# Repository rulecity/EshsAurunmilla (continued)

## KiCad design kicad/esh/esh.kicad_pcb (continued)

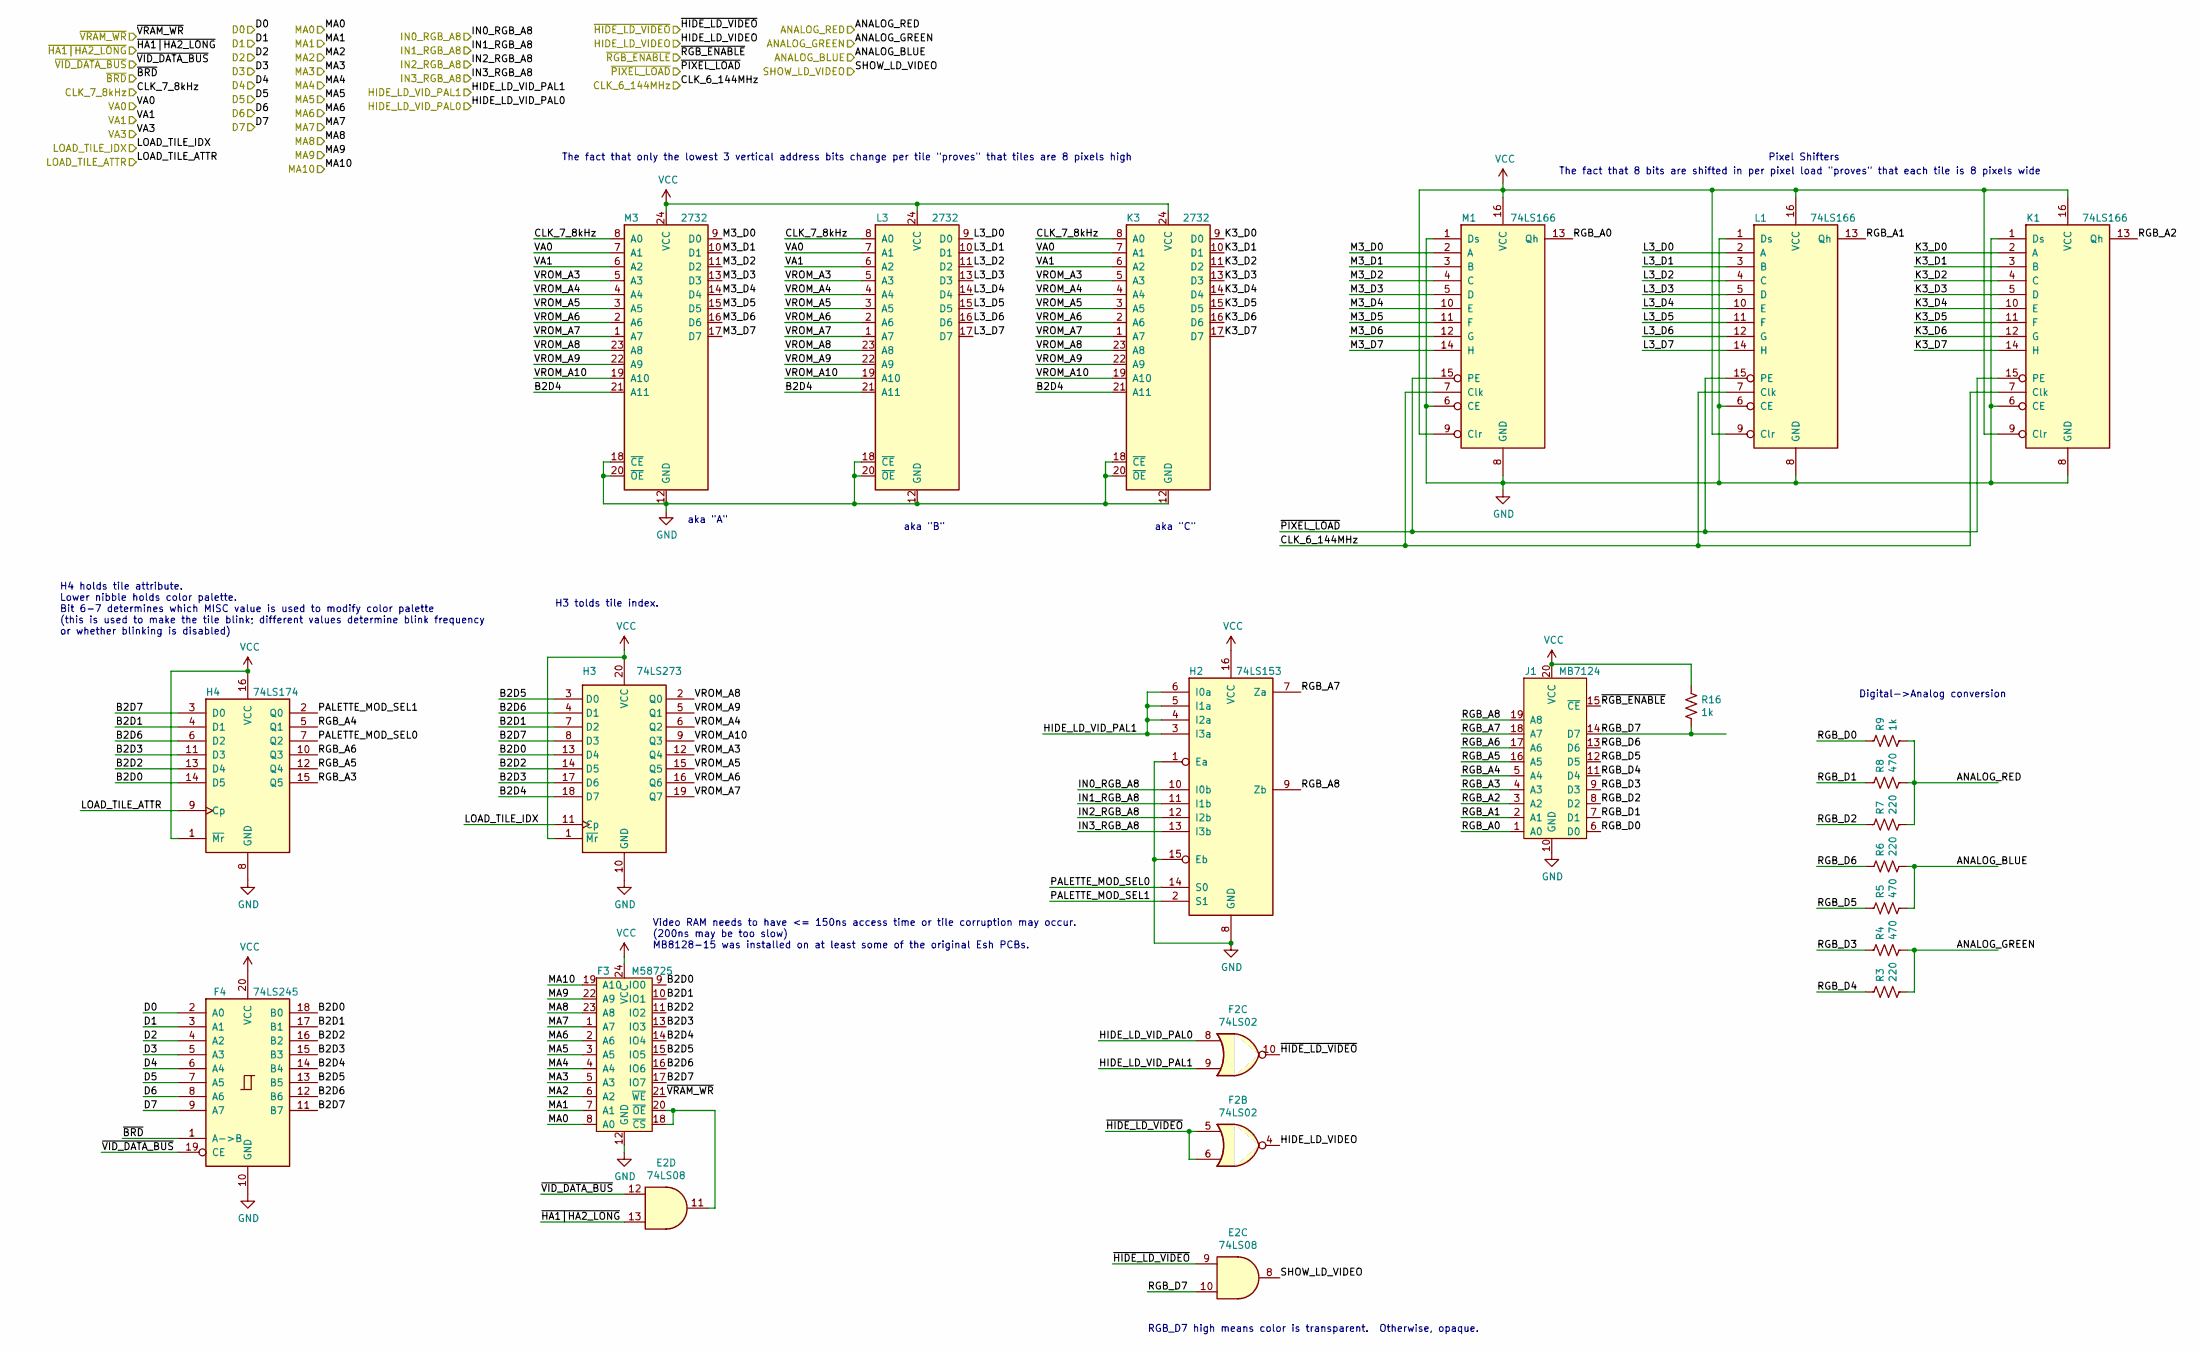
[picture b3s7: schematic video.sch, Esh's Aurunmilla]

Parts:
E2: 74LS08; DIP-14_W7.62mm_Socket
F2: 74LS02; DIP-14_W7.62mm_Socket
F3: M58725; DIP-24_W15.24mm_Socket
F4: 74LS245; DIP-20_W7.62mm_Socket
H2: 74LS153; DIP-16_W7.62mm_Socket
H3: 74LS273; DIP-20_W7.62mm_Socket
H4: 74LS174; DIP-16_W7.62mm_Socket
J1: MB7124; DIP-20_W7.62mm_Socket
K1: 74LS166; DIP-16_W7.62mm_Socket
K3: 2732; DIP-24_W15.24mm_Socket
L1: 74LS166; DIP-16_W7.62mm_Socket
L3: 2732; DIP-24_W15.24mm_Socket
M1: 74LS166; DIP-16_W7.62mm_Socket
M3: 2732; DIP-24_W15.24mm_Socket
R3, R6, R7: 220; R_Axial_DIN0207_L6.3mm_D2.5mm_P10.16mm_Horizontal
R4, R5, R8: 470; R_Axial_DIN0207_L6.3mm_D2.5mm_P10.16mm_Horizontal
R9, R16: 1k; R_Axial_DIN0207_L6.3mm_D2.5mm_P10.16mm_Horizontal

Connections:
/ANALOG_BLUE: R5.2, R6.2; also elsewhere on the board
/ANALOG_GREEN: R3.2, R4.2; also elsewhere on the board
/ANALOG_RED: R7.2, R8.2, R9.2; also elsewhere on the board
/CLK_6_144MHz: K1.7 (Clk), L1.7 (Clk), M1.7 (Clk); also elsewhere on the board
/CLK_7_8kHz: K3.8 (A0), L3.8 (A0), M3.8 (A0); also elsewhere on the board
/D0: F4.2 (A0); also elsewhere on the board
/D1: F4.3 (A1); also elsewhere on the board
/D2: F4.4 (A2); also elsewhere on the board
/D3: F4.5 (A3); also elsewhere on the board
/D4: F4.6 (A4); also elsewhere on the board
/D5: F4.7 (A5); also elsewhere on the board
/D6: F4.8 (A6); also elsewhere on the board
/D7: F4.9 (A7); also elsewhere on the board
/HIDE_LD_VIDEO: F2.4; also elsewhere on the board
/HIDE_LD_VID_PAL0: F2.8; also elsewhere on the board
/HIDE_LD_VID_PAL1: F2.9, H2.3 (I3a), H2.4 (I2a), H2.5 (I1a), H2.6 (I0a); also elsewhere on the board
/IN0_RGB_A8: H2.10 (I0b); also elsewhere on the board
/IN1_RGB_A8: H2.11 (I1b); also elsewhere on the board
/IN2_RGB_A8: H2.12 (I2b); also elsewhere on the board
/IN3_RGB_A8: H2.13 (I3b); also elsewhere on the board
/LOAD_TILE_ATTR: H4.9 (Cp); also elsewhere on the board
/LOAD_TILE_IDX: H3.11 (Cp); also elsewhere on the board
/MA0: F3.8 (A0); also elsewhere on the board
/MA1: F3.7 (A1); also elsewhere on the board
/MA2: F3.6 (A2); also elsewhere on the board
/MA3: F3.5 (A3); also elsewhere on the board
/MA4: F3.4 (A4); also elsewhere on the board
/MA5: F3.3 (A5); also elsewhere on the board
/MA6: F3.2 (A6); also elsewhere on the board
/MA7: F3.1 (A7); also elsewhere on the board
/MA8: F3.23 (A8); also elsewhere on the board
/MA9: F3.22 (A9); also elsewhere on the board
/MA10: F3.19 (A10); also elsewhere on the board
/SHOW_LD_VIDEO: E2.8; also elsewhere on the board
/VA0: K3.7 (A1), L3.7 (A1), M3.7 (A1); also elsewhere on the board
/VA1: K3.6 (A2), L3.6 (A2), M3.6 (A2); also elsewhere on the board
/video/B2D0: F3.9 (IO0), F4.18 (B0), H3.13 (D4), H4.14 (D5)
/video/B2D1: F3.10 (IO1), F4.17 (B1), H3.7 (D2), H4.4 (D1)
/video/B2D2: F3.11 (IO2), F4.16 (B2), H3.14 (D5), H4.13 (D4)
/video/B2D3: F3.13 (IO3), F4.15 (B3), H3.17 (D6), H4.11 (D3)
/video/B2D4: F3.14 (IO4), F4.14 (B4), H3.18 (D7), K3.21 (A11), L3.21 (A11), M3.21 (A11)
/video/B2D5: F3.15 (IO5), F4.13 (B5), H3.3 (D0)
/video/B2D6: F3.16 (IO6), F4.12 (B6), H3.4 (D1), H4.6 (D2)
/video/B2D7: F3.17 (IO7), F4.11 (B7), H3.8 (D3), H4.3 (D0)
/video/K3_D0: K1.2 (A), K3.9 (D0)
/video/K3_D1: K1.3 (B), K3.10 (D1)
/video/K3_D2: K1.4 (C), K3.11 (D2)
/video/K3_D3: K1.5 (D), K3.13 (D3)
/video/K3_D4: K1.10 (E), K3.14 (D4)
/video/K3_D5: K1.11 (F), K3.15 (D5)
/video/K3_D6: K1.12 (G), K3.16 (D6)
/video/K3_D7: K1.14 (H), K3.17 (D7)
/video/L3_D0: L1.2 (A), L3.9 (D0)
/video/L3_D1: L1.3 (B), L3.10 (D1)
/video/L3_D2: L1.4 (C), L3.11 (D2)
/video/L3_D3: L1.5 (D), L3.13 (D3)
/video/L3_D4: L1.10 (E), L3.14 (D4)
/video/L3_D5: L1.11 (F), L3.15 (D5)
/video/L3_D6: L1.12 (G), L3.16 (D6)
/video/L3_D7: L1.14 (H), L3.17 (D7)
/video/M3_D0: M1.2 (A), M3.9 (D0)
/video/M3_D1: M1.3 (B), M3.10 (D1)
/video/M3_D2: M1.4 (C), M3.11 (D2)
/video/M3_D3: M1.5 (D), M3.13 (D3)
/video/M3_D4: M1.10 (E), M3.14 (D4)
/video/M3_D5: M1.11 (F), M3.15 (D5)
/video/M3_D6: M1.12 (G), M3.16 (D6)
/video/M3_D7: M1.14 (H), M3.17 (D7)
/video/PALETTE_MOD_SEL0: H2.14 (S0), H4.7 (Q2)
/video/PALETTE_MOD_SEL1: H2.2 (S1), H4.2 (Q0)
/video/RGB_A0: J1.1 (A0), M1.13 (Qh)
/video/RGB_A1: J1.2 (A1), L1.13 (Qh)
/video/RGB_A2: J1.3 (A2), K1.13 (Qh)
/video/RGB_A3: H4.15 (Q5), J1.4 (A3)
/video/RGB_A4: H4.5 (Q1), J1.5 (A4)
/video/RGB_A5: H4.12 (Q4), J1.16 (A5)
/video/RGB_A6: H4.10 (Q3), J1.17 (A6)
/video/RGB_A7: H2.7 (Za), J1.18 (A7)
/video/RGB_A8: H2.9 (Zb), J1.19 (A8)
/video/RGB_D0: J1.6 (D0), R9.1
/video/RGB_D1: J1.7 (D1), R8.1
/video/RGB_D2: J1.8 (D2), R7.1
/video/RGB_D3: J1.9 (D3), R4.1
/video/RGB_D4: J1.11 (D4), R3.1
/video/RGB_D5: J1.12 (D5), R5.1
/video/RGB_D6: J1.13 (D6), R6.1
/video/RGB_D7: E2.10, J1.14 (D7), R16.2
/video/VROM_A3: H3.12 (Q4), K3.5 (A3), L3.5 (A3), M3.5 (A3)
/video/VROM_A4: H3.6 (Q2), K3.4 (A4), L3.4 (A4), M3.4 (A4)
/video/VROM_A5: H3.15 (Q5), K3.3 (A5), L3.3 (A5), M3.3 (A5)
/video/VROM_A6: H3.16 (Q6), K3.2 (A6), L3.2 (A6), M3.2 (A6)
/video/VROM_A7: H3.19 (Q7), K3.1 (A7), L3.1 (A7), M3.1 (A7)
/video/VROM_A8: H3.2 (Q0), K3.23 (A8), L3.23 (A8), M3.23 (A8)
/video/VROM_A9: H3.5 (Q1), K3.22 (A9), L3.22 (A9), M3.22 (A9)
/video/VROM_A10: H3.9 (Q3), K3.19 (A10), L3.19 (A10), M3.19 (A10)
/~BRD: F4.1 (A->B); also elsewhere on the board
/~HA1|HA2_LONG: E2.13; also elsewhere on the board
/~HIDE_LD_VIDEO: E2.9, F2.5, F2.6, F2.10; also elsewhere on the board
/~PIXEL_LOAD: K1.15 (PE), L1.15 (PE), M1.15 (PE); also elsewhere on the board
/~RGB_ENABLE: J1.15 (~CE); also elsewhere on the board
/~VID_DATA_BUS: E2.12, F4.19 (CE); also elsewhere on the board
/~VRAM_WR: F3.21 (~WE); also elsewhere on the board
GND: F3.12 (GND), F4.10 (GND), H2.1 (Ea), H2.8 (GND), H2.15 (Eb), H3.10 (GND), H4.8 (GND), J1.10 (GND), K1.1 (Ds), K1.6 (CE), K1.8 (GND), K3.12 (GND), K3.18 (~CE), K3.20 (~OE), L1.1 (Ds), L1.6 (CE), L1.8 (GND), L3.12 (GND), L3.18 (~CE), L3.20 (~OE), M1.1 (Ds), M1.6 (CE), M1.8 (GND), M3.12 (GND), M3.18 (~CE), M3.20 (~OE); also elsewhere on the board
unnamed: E2.11, F3.18 (~CS), F3.20 (~OE)
VCC: F3.24 (VCC), F4.20 (VCC), H2.16 (VCC), H3.1 (~Mr), H3.20 (VCC), H4.1 (~Mr), H4.16 (VCC), J1.20 (VCC), K1.9 (Clr), K1.16 (VCC), K3.24 (VCC), L1.9 (Clr), L1.16 (VCC), L3.24 (VCC), M1.9 (Clr), M1.16 (VCC), M3.24 (VCC), R16.1; also elsewhere on the board

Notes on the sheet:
RGB_D7 high means color is transparent. Otherwise, opaque.
aka "A"
aka "B"
aka "C"
Pixel Shifters
H4 holds tile attribute. Lower nibble holds color palette. Bit 6-7 determines which MISC value is used to modify color palette (this is used to make the tile blink; different values determine blink frequency or whether blinking is disabled)
H3 tolds tile index.
The fact that only the lowest 3 vertical address bits change per tile "proves" that tiles are 8 pixels high
The fact that 8 bits are shifted in per pixel load "proves" that each tile is 8 pixels wide
Digital->Analog conversion
Video RAM needs to have <= 150ns access time or tile corruption may occur. (200ns may be too slow) MB8128-15 was installed on at least some of the original Esh PCBs.

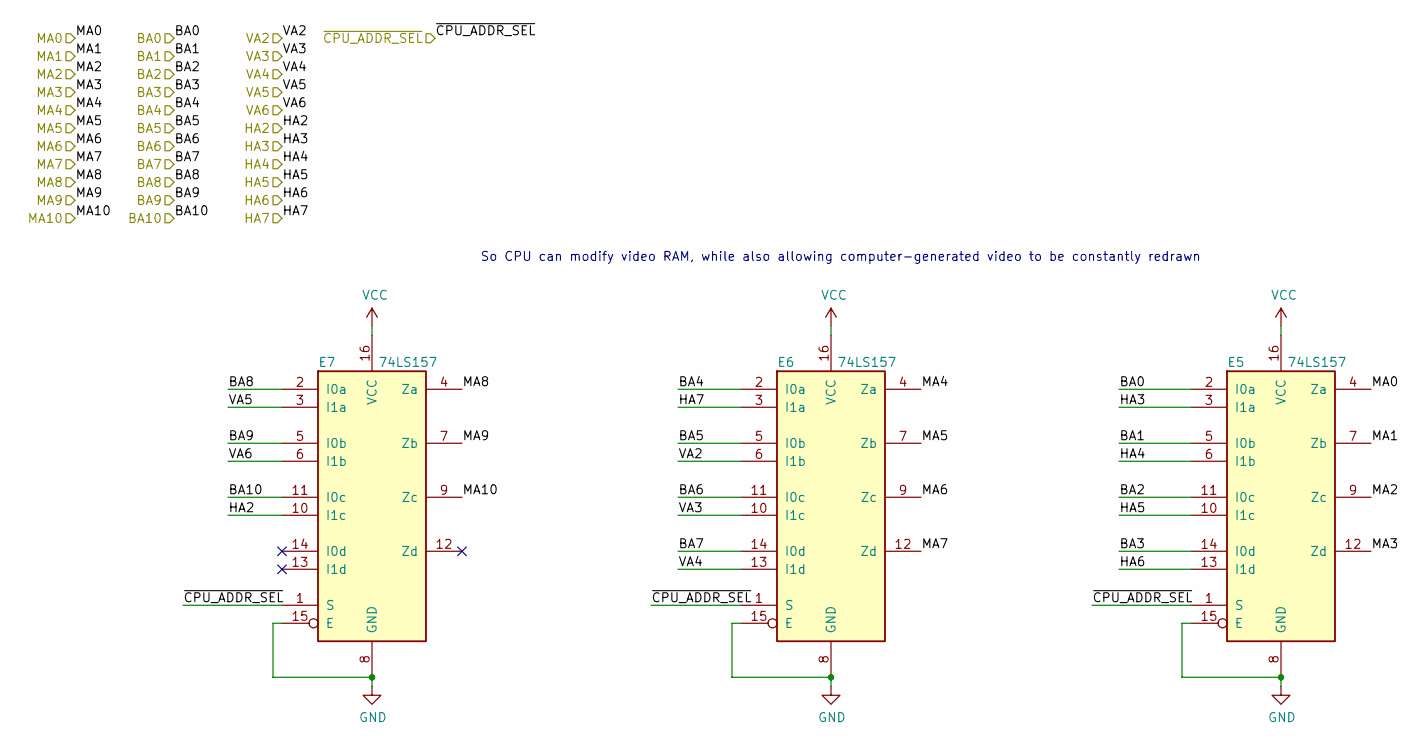
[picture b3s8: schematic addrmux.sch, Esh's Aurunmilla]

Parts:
E5, E6, E7: 74LS157; DIP-16_W7.62mm_Socket

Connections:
/BA0: E5.2 (I0a); also elsewhere on the board
/BA1: E5.5 (I0b); also elsewhere on the board
/BA2: E5.11 (I0c); also elsewhere on the board
/BA3: E5.14 (I0d); also elsewhere on the board
/BA4: E6.2 (I0a); also elsewhere on the board
/BA5: E6.5 (I0b); also elsewhere on the board
/BA6: E6.11 (I0c); also elsewhere on the board
/BA7: E6.14 (I0d); also elsewhere on the board
/BA8: E7.2 (I0a); also elsewhere on the board
/BA9: E7.5 (I0b); also elsewhere on the board
/BA10: E7.11 (I0c); also elsewhere on the board
/HA2: E7.10 (I1c); also elsewhere on the board
/HA3: E5.3 (I1a); also elsewhere on the board
/HA4: E5.6 (I1b); also elsewhere on the board
/HA5: E5.10 (I1c); also elsewhere on the board
/HA6: E5.13 (I1d); also elsewhere on the board
/HA7: E6.3 (I1a); also elsewhere on the board
/MA0: E5.4 (Za); also elsewhere on the board
/MA1: E5.7 (Zb); also elsewhere on the board
/MA2: E5.9 (Zc); also elsewhere on the board
/MA3: E5.12 (Zd); also elsewhere on the board
/MA4: E6.4 (Za); also elsewhere on the board
/MA5: E6.7 (Zb); also elsewhere on the board
/MA6: E6.9 (Zc); also elsewhere on the board
/MA7: E6.12 (Zd); also elsewhere on the board
/MA8: E7.4 (Za); also elsewhere on the board
/MA9: E7.7 (Zb); also elsewhere on the board
/MA10: E7.9 (Zc); also elsewhere on the board
/VA2: E6.6 (I1b); also elsewhere on the board
/VA3: E6.10 (I1c); also elsewhere on the board
/VA4: E6.13 (I1d); also elsewhere on the board
/VA5: E7.3 (I1a); also elsewhere on the board
/VA6: E7.6 (I1b); also elsewhere on the board
/~CPU_ADDR_SEL: E5.1 (S), E6.1 (S), E7.1 (S); also elsewhere on the board
GND: E5.8 (GND), E5.15 (E), E6.8 (GND), E6.15 (E), E7.8 (GND), E7.15 (E); also elsewhere on the board
VCC: E5.16 (VCC), E6.16 (VCC), E7.16 (VCC); also elsewhere on the board

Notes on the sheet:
So CPU can modify video RAM, while also allowing computer-generated video to be constantly redrawn

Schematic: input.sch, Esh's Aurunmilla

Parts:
A2: 74LS253; DIP-16_W7.62mm_Socket
B2: 74LS253; DIP-16_W7.62mm_Socket
C2: 74LS253; DIP-16_W7.62mm_Socket
INP_C3, INP_C4, INP_C7, INP_C11, INP_C12, INP_C13, INP_C17, INP_C18, INP_C19, INP_C21, INP_C22, INP_C23, INP_C24, INP_C25: 0.1uF; R_Axial_DIN0204_L3.6mm_D1.6mm_P5.08mm_Horizontal
RA1, RA2, RA3: 1k; R_Array_SIP9
RA4, RA5, RA6, RA7, RA8, RA9: 220; R_Array_SIP8

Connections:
/BA0: A2.14 (A0), B2.14 (A0), C2.14 (A0); also elsewhere on the board
/BA1: A2.2 (A1), B2.2 (A1), C2.2 (A1); also elsewhere on the board
/BD0: C2.7 (Za); also elsewhere on the board
/BD1: C2.9 (Zb); also elsewhere on the board
/BD2: B2.7 (Za); also elsewhere on the board
/BD3: B2.9 (Zb); also elsewhere on the board
/BD4: A2.7 (Za); also elsewhere on the board
/BD5: A2.9 (Zb); also elsewhere on the board
/RA1_P5: RA1.5 (R4), RA4.4 (R2.2); also elsewhere on the board
/RA1_P9: RA1.9 (R8), RA4.8 (R4.2); also elsewhere on the board
/RA2_P4: RA2.4 (R3), RA5.4 (R2.2); also elsewhere on the board
/RA2_P7: RA2.7 (R6), RA8.6 (R3.2); also elsewhere on the board
/RA3_P3: RA3.3 (R2), RA6.2 (R1.2); also elsewhere on the board
/RA3_P8: RA3.8 (R7), RA6.8 (R4.2); also elsewhere on the board
/input/A2_P3: A2.3 (I3a), RA7.3 (R2.1)
/input/A2_P4: A2.4 (I2a), RA4.3 (R2.1)
/input/A2_P10: A2.10 (I0b), RA4.5 (R3.1)
/input/A2_P12: A2.12 (I2b), RA4.7 (R4.1)
/input/A2_P13: A2.13 (I3b), RA7.7 (R4.1)
/input/B2_P4: B2.4 (I2a), RA5.3 (R2.1)
/input/B2_P12: B2.12 (I2b), RA8.5 (R3.1)
/input/B2_P13: B2.13 (I3b), RA5.5 (R3.1)
/input/C2_P4: C2.4 (I2a), RA6.1 (R1.1)
/input/C2_P12: C2.12 (I2b), RA6.7 (R4.1)
/input/~DBNC_ACTION: A2.5 (I1a), INP_C3.1, RA7.1 (R1.1)
/input/~DBNC_ACTION2: A2.11 (I1b), INP_C7.1, RA7.5 (R3.1)
/input/~DBNC_COIN1: C2.6 (I0a), INP_C19.1, RA9.1 (R1.1)
/input/~DBNC_COIN2: C2.10 (I0b), INP_C23.1, RA9.5 (R3.1)
/input/~DBNC_DOWN: C2.11 (I1b), INP_C24.1, RA6.5 (R3.1)
/input/~DBNC_LEFT: B2.5 (I1a), INP_C12.1, RA5.1 (R1.1)
/input/~DBNC_RIGHT: B2.11 (I1b), INP_C18.1, RA5.7 (R4.1)
/input/~DBNC_START1: B2.6 (I0a), INP_C11.1, RA8.1 (R1.1)
/input/~DBNC_START2: B2.10 (I0b), INP_C17.1, RA8.7 (R4.1)
/input/~DBNC_TEST: A2.6 (I0a), INP_C4.1, RA4.1 (R1.1)
/input/~DBNC_UNK1: C2.3 (I3a), INP_C21.1, RA9.3 (R2.1)
/input/~DBNC_UNK2: C2.13 (I3b), INP_C25.1, RA9.7 (R4.1)
/input/~DBNC_UNK3: B2.3 (I3a), INP_C13.1, RA8.3 (R2.1)
/input/~DBNC_UP: C2.5 (I1a), INP_C22.1, RA6.3 (R2.1)
/~F0-F3_PORT_RD: A2.1 (OEa), A2.15 (OEb), B2.1 (OEa), B2.15 (OEb), C2.1 (OEa), C2.15 (OEb); also elsewhere on the board
/~SWITCH_ACTION: RA1.2 (R1), RA7.2 (R1.2); also elsewhere on the board
/~SWITCH_ACTION2: RA1.6 (R5), RA7.6 (R3.2); also elsewhere on the board
/~SWITCH_COIN1: RA3.2 (R1), RA9.2 (R1.2); also elsewhere on the board
/~SWITCH_COIN2: RA3.7 (R6), RA9.6 (R3.2); also elsewhere on the board
/~SWITCH_DOWN: RA3.6 (R5), RA6.6 (R3.2); also elsewhere on the board
/~SWITCH_LEFT: RA2.2 (R1), RA5.2 (R1.2); also elsewhere on the board
/~SWITCH_RIGHT: RA2.8 (R7), RA5.8 (R4.2); also elsewhere on the board
/~SWITCH_START1: RA2.3 (R2), RA8.2 (R1.2); also elsewhere on the board
/~SWITCH_START2: RA2.9 (R8), RA8.8 (R4.2); also elsewhere on the board
/~SWITCH_TEST: RA1.3 (R2), RA4.2 (R1.2); also elsewhere on the board
/~SWITCH_UNK1: RA3.5 (R4), RA9.4 (R2.2); also elsewhere on the board
/~SWITCH_UNK2: RA3.9 (R8), RA9.8 (R4.2); also elsewhere on the board
/~SWITCH_UNK3: RA2.5 (R4), RA8.4 (R2.2); also elsewhere on the board
/~SWITCH_UP: RA3.4 (R3), RA6.4 (R2.2); also elsewhere on the board
GND: A2.8 (GND), B2.8 (GND), C2.8 (GND), INP_C3.2, INP_C4.2, INP_C7.2, INP_C11.2, INP_C12.2, INP_C13.2, INP_C17.2, INP_C18.2, INP_C19.2, INP_C21.2, INP_C22.2, INP_C23.2, INP_C24.2, INP_C25.2; also elsewhere on the board
unnamed: RA1.4 (R3), RA7.4 (R2.2)
unnamed: RA1.7 (R6), RA4.6 (R3.2)
unnamed: RA1.8 (R7), RA7.8 (R4.2)
unnamed: RA2.6 (R5), RA5.6 (R3.2)
VCC: A2.16 (VCC), B2.16 (VCC), C2.16 (VCC), RA1.1 (common), RA2.1 (common), RA3.1 (common); also elsewhere on the board

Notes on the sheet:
Unused inputs are connected to pull-ups as a precaution

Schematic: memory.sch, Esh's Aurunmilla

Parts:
B8: MB8416-20; DIP-24_W15.24mm_Socket
BAT1: 3-51FT-P, 3.6V; Battery_3-51FT-P
C8: 2764; DIP-28_W15.24mm
CP_B8: 0.1uF; R_Axial_DIN0204_L3.6mm_D1.6mm_P5.08mm_Horizontal
D8: 2764; DIP-28_W15.24mm
DIODE2, DIODE3: 1N4148; D_T-1_P10.16mm_Horizontal
E8: 2764; DIP-28_W15.24mm
F8: 2764; DIP-28_W15.24mm
H8: 2764; DIP-28_W15.24mm
R24: 470; R_Axial_DIN0207_L6.3mm_D2.5mm_P10.16mm_Horizontal
R25: 10k; R_Axial_DIN0207_L6.3mm_D2.5mm_P10.16mm_Horizontal

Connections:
/A0: B8.8 (A0), C8.10 (A0), D8.10 (A0), E8.10 (A0), F8.10 (A0), H8.10 (A0); also elsewhere on the board
/A1: B8.7 (A1), C8.9 (A1), D8.9 (A1), E8.9 (A1), F8.9 (A1), H8.9 (A1); also elsewhere on the board
/A2: B8.6 (A2), C8.8 (A2), D8.8 (A2), E8.8 (A2), F8.8 (A2), H8.8 (A2); also elsewhere on the board
/A3: B8.5 (A3), C8.7 (A3), D8.7 (A3), E8.7 (A3), F8.7 (A3), H8.7 (A3); also elsewhere on the board
/A4: B8.4 (A4), C8.6 (A4), D8.6 (A4), E8.6 (A4), F8.6 (A4), H8.6 (A4); also elsewhere on the board
/A5: B8.3 (A5), C8.5 (A5), D8.5 (A5), E8.5 (A5), F8.5 (A5), H8.5 (A5); also elsewhere on the board
/A6: B8.2 (A6), C8.4 (A6), D8.4 (A6), E8.4 (A6), F8.4 (A6), H8.4 (A6); also elsewhere on the board
/A7: B8.1 (A7), C8.3 (A7), D8.3 (A7), E8.3 (A7), F8.3 (A7), H8.3 (A7); also elsewhere on the board
/A8: B8.23 (A8), C8.25 (A8), D8.25 (A8), E8.25 (A8), F8.25 (A8), H8.25 (A8); also elsewhere on the board
/A9: B8.22 (A9), C8.24 (A9), D8.24 (A9), E8.24 (A9), F8.24 (A9), H8.24 (A9); also elsewhere on the board
/A10: B8.19 (A10), C8.21 (A10), D8.21 (A10), E8.21 (A10), F8.21 (A10), H8.21 (A10); also elsewhere on the board
/A11: C8.23 (A11), D8.23 (A11), E8.23 (A11), F8.23 (A11), H8.23 (A11); also elsewhere on the board
/A12: C8.2 (A12), D8.2 (A12), E8.2 (A12), F8.2 (A12), H8.2 (A12); also elsewhere on the board
/D0: B8.9 (IO0), C8.11 (D0), D8.11 (D0), E8.11 (D0), F8.11 (D0), H8.11 (D0); also elsewhere on the board
/D1: B8.10 (IO1), C8.12 (D1), D8.12 (D1), E8.12 (D1), F8.12 (D1), H8.12 (D1); also elsewhere on the board
/D2: B8.11 (IO2), C8.13 (D2), D8.13 (D2), E8.13 (D2), F8.13 (D2), H8.13 (D2); also elsewhere on the board
/D3: B8.13 (IO3), C8.15 (D3), D8.15 (D3), E8.15 (D3), F8.15 (D3), H8.15 (D3); also elsewhere on the board
/D4: B8.14 (IO4), C8.16 (D4), D8.16 (D4), E8.16 (D4), F8.16 (D4), H8.16 (D4); also elsewhere on the board
/D5: B8.15 (IO5), C8.17 (D5), D8.17 (D5), E8.17 (D5), F8.17 (D5), H8.17 (D5); also elsewhere on the board
/D6: B8.16 (IO6), C8.18 (D6), D8.18 (D6), E8.18 (D6), F8.18 (D6), H8.18 (D6); also elsewhere on the board
/D7: B8.17 (IO7), C8.19 (D7), D8.19 (D7), E8.19 (D7), F8.19 (D7), H8.19 (D7); also elsewhere on the board
/RAM_PWR: B8.24 (VCC), CP_B8.1, DIODE2.1 (K), DIODE3.1 (K), R24.2, R25.2; also elsewhere on the board
/~RAM_B8: B8.18 (~CS), R25.1; also elsewhere on the board
/~RD: B8.20 (~OE), C8.22 (~OE), D8.22 (~OE), E8.22 (~OE), F8.22 (~OE), H8.22 (~OE); also elsewhere on the board
/~ROM_C8: C8.20 (~CE); also elsewhere on the board
/~ROM_D8: D8.20 (~CE); also elsewhere on the board
/~ROM_E8: E8.20 (~CE); also elsewhere on the board
/~ROM_F8: F8.20 (~CE); also elsewhere on the board
/~ROM_H8: H8.20 (~CE); also elsewhere on the board
/~WR: B8.21 (~WE), C8.27 (~PGM), D8.27 (~PGM), E8.27 (~PGM), F8.27 (~PGM), H8.27 (~PGM); also elsewhere on the board
GND: B8.12 (GND), BAT1.2 (-), C8.14 (GND), CP_B8.2, D8.14 (GND), E8.14 (GND), F8.14 (GND), H8.14 (GND); also elsewhere on the board
unnamed: BAT1.1 (+), DIODE3.2 (A), R24.1
VCC: C8.1 (VPP), C8.28 (VCC), D8.1 (VPP), D8.28 (VCC), DIODE2.2 (A), E8.1 (VPP), E8.28 (VCC), F8.1 (VPP), F8.28 (VCC), H8.1 (VPP), H8.28 (VCC); also elsewhere on the board

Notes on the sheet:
Address Bus
Data Bus
When powered on, RAM_PWR is VCC - 0.6V (measured VCC at 4.8V, RAM_PWR at 4.2V) When powered off, RAM_PWR is the battery's voltage
Original battery manufacturer is YUASA
This is the CPU's RAM. Generic 6116 RAM should work as a replacement.

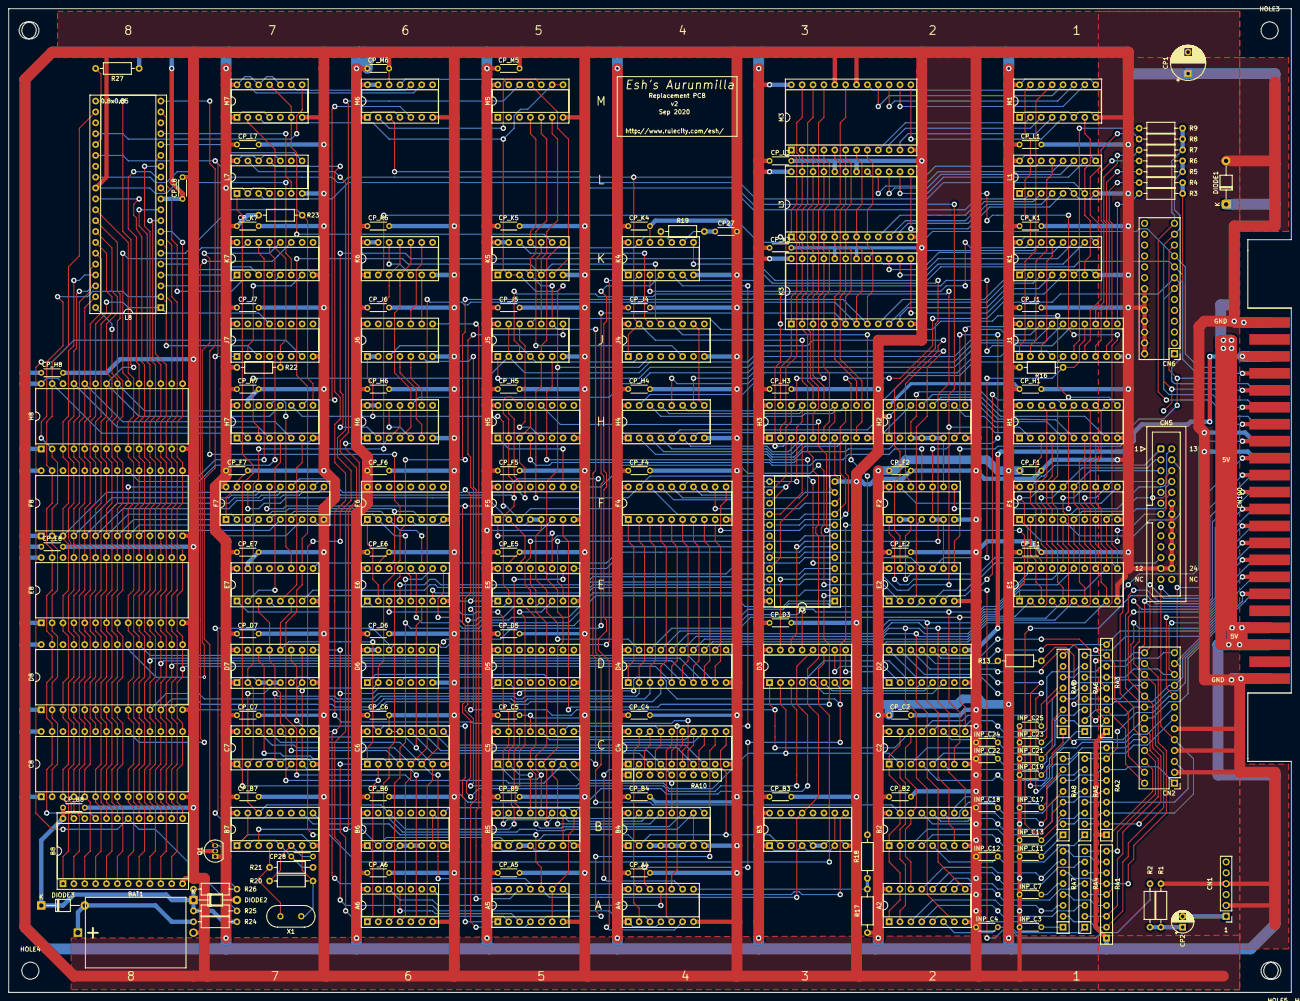
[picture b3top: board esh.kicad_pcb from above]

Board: 2 copper layers, 299.7 x 229.9 mm, 188 parts (0 on the bottom side), 330 nets.

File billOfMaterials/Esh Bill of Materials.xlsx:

Quantity | Reference | Manufacturer | Manufacturer Part Number | Distributor | Dist. Part Number | Note | Pins
1.0 |  |  |  | DigiKey | AE10008-ND | 40-pin socket
1.0 | L8 |  |  | jameco.com |  | Z80 CPU | 40.0
2.0 |  |  |  | DigiKey | AE10004-ND | 28-pin socket
2.0 | H8 F8 |  |  | jameco.com |  | 2764.0 | 28.0
5.0 |  |  |  | DigiKey | AE10001-ND | 24-pin socket
2.0 | J1 socket alternative |  |  | DigiKey | S7043-ND | To connect to PROM replacement PCB
1.0 | F3 |  |  | jameco.com |  | RAM 6116 150ms | 24.0
1.0 | B8 |  |  | jameco.com |  | RAM 6116 200ms | 24.0
3.0 | M3 L3 K3 |  |  | jameco.com |  | 2732.0 | 24.0
8.0 |  |  |  | DigiKey | AE9998-ND | 20-pin socket
3.0 | C1,C3,C4 |  |  | DigiKey | 296-1657-5-ND | 74LS273 | 20.0
2.0 | D4,F4 |  |  | DigiKey | 296-1655-5-ND | 74LS245 | 20.0
2.0 | F1 E1 |  |  | DigiKey | 296-1660-5-ND | 74LS373 | 20.0
1.0 | F7 |  |  | DigiKey | 296-1653-5-ND | 74LS244 | 20.0
0.0 | J1 |  | MB7124 |  |  | Use CPLD instead. PROM is too rare. | 20.0
28.0 |  |  |  | DigiKey | AE9992-ND | 16-pin socket
4.0 | C5,C6 socket alternative |  |  | DigiKey | S7041-ND | To connect to PROM replacement PCB
1.0 | B7 |  |  | DigiKey | 296-3702-5-ND | 74LS368 | 16.0
3.0 | A2,B2,C2 |  |  | DigiKey | 296-33981-5-ND | 74LS253 | 16.0
0.0 | C5,C6 |  | MB7052 | DigiKey |  | Use CPLD instead. PROMs overheat. | 16.0
1.0 | D2 |  |  | DigiKey | 497-2344-5-ND | ULN2003 | 16.0
6.0 | B6,B5,B4,B3,D7,C7 |  |  | DigiKey | 296-1646-5-ND | 74LS161 | 16.0
1.0 | D3 |  |  | DigiKey | 296-14889-5-ND | 74LS259 | 16.0
3.0 | D5 H5 J4 |  |  | DigiKey | 296-1640-5-ND | 74LS139 | 16.0
3.0 | E7 E6 E5 |  |  | DigiKey | 296-1645-5-ND | 74LS157 | 16.0
1.0 | H2 |  |  | DigiKey | 296-3654-5-ND | 74LS153 | 16.0
1.0 | H4 |  |  | DigiKey | 296-3664-5-ND | 74LS174 | 16.0
1.0 | H7 |  |  | DigiKey | 296-3701-5-ND | 74LS367 | 16.0
1.0 | J7 |  |  | DigiKey | 296-3655-5-ND | 74LS156 | 16.0
3.0 | K7 F6 F5 |  |  | DigiKey | 296-1639-5-ND | 74LS138 | 16.0
3.0 | M1 L1 K1 |  |  | DigiKey | 296-3662-5-ND | 74LS166 | 16.0
16.0 |  |  |  | DigiKey | AE9989-ND | 14-pin socket
2.0 | A2,A5 |  |  | DigiKey | 296-1633-5-ND | 74LS08 | 14.0
1.0 | A4 |  |  | DigiKey | 296-1669-5-ND | 74LS86 | 14.0
1.0 | A6 |  |  | DigiKey | 296-3693-5-ND | 74LS30 | 14.0
1.0 | D6 |  |  | DigiKey | 296-33952-5-ND | 74LS107 | 14.0
2.0 | F2 M5 |  |  | DigiKey | 296-1627-5-ND | 74LS02 | 14.0
2.0 | J5 K4 |  |  | DigiKey | 296-1658-5-ND | 74LS32 | 14.0
1.0 | J6 |  |  | DigiKey | 296-1626-ND | 74LS00 | 14.0
1.0 | K5 |  |  | DigiKey | 296-1634-5-ND | 74LS10 | 14.0
5.0 | L7 M7 M6 K6 H6 |  |  | DigiKey | 296-1668-5-ND | 74LS74 | 14.0
1.0 | BAT1 |  |  |  |  | 3-51FT-P
1.0 | CP1 |  |  | DigiKey | 493-1743-ND | 470uF, 16V. 8mm Diameter, 5mm Pin
1.0 | CP2 |  |  | DigiKey | 493-15966-1-ND | 10uF, 16V. 5mm diameter, 2.5mm pin
1.0 | CP27 |  |  | DigiKey | 399-14048-ND | 350pF
1.0 | CP28 |  |  | DigiKey | 399-8916-ND | 20pF, to match crystal. Mike Treu said 33pF worked better for him.
1.0 | CN1 | JST | B6P-SHF-1AA(LF)(SN) | DigiKey | 455-4181-ND | Audio connector
1.0 | CN5 | Amphenol | 71918-126LF | DigiKey | 609-1756-ND | LD-V1000 Connector
69.0 | CP# |  |  | DigiKey | 399-9759-ND | 0.1uF
1.0 | DIODE1 |  |  | DigiKey | BZX85C6V2-TAPGICT-ND | BZX85C6V2
2.0 | DIODE2,DIODE3 |  |  | DigiKey | 1N4148FS-ND | 1N4148
1.0 | Q1 | Microchip | MCP120-450GI/TO | DigiKey | MCP120-450GI/TO-ND
1.0 | R1 |  |  | DigiKey | CF14JT1K20CT-ND | 1.2k
1.0 | R13 |  |  | DigiKey | S100HCT-ND | 100 Ohm, 1/2W
5.0 | R17 R27 R22 R16 R9 |  |  | DigiKey | CF14JT1K00CT-ND | 1k
1.0 | R18 |  |  | DigiKey | CF14JT100RCT-ND | 100.0
3.0 | R2 R26 R25 |  |  | DigiKey | CF14JT10K0CT-ND | 10k
2.0 | R21 R20 |  |  | DigiKey | CF14JT330RCT-ND | 330.0
5.0 | R23 R19 R7 R6 R3 |  |  | DigiKey | CF14JT220RCT-ND | 220.0
4.0 | R8 R5 R4 R24 |  |  | DigiKey | CF14JT470RCT-ND | 470.0
4.0 | RA10 RA1 RA2 RA3 |  |  | DigiKey | 4609X-101-102LF-ND | 1k array
6.0 | RA4 RA7 RA5 RA8 RA6 RA9 |  |  | DigiKey | 770-83-R220P-ND | 220, series
1.0 | X1 | Fox | FC4STCBMF18.432-BAG200 | DigiKey | 631-1109-ND

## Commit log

2024-06-08 added main Esh PCB - kicad v5 project
2024-06-08 added Esh's sync prom replacement PCB
2024-06-08 moved CPLD into esh.lib
2024-06-08 added Esh color PROM replacement PCB
2024-06-08 Added Esh's sync/timing PROM replacement and color PROM replacement code
2024-06-08 added bill of materials files for the three Esh PCBs
2024-06-08 added source code to test ROM
2024-06-16 added BofM for LDP and sound cables
2024-07-05 Update README.md
    offering commercial support
